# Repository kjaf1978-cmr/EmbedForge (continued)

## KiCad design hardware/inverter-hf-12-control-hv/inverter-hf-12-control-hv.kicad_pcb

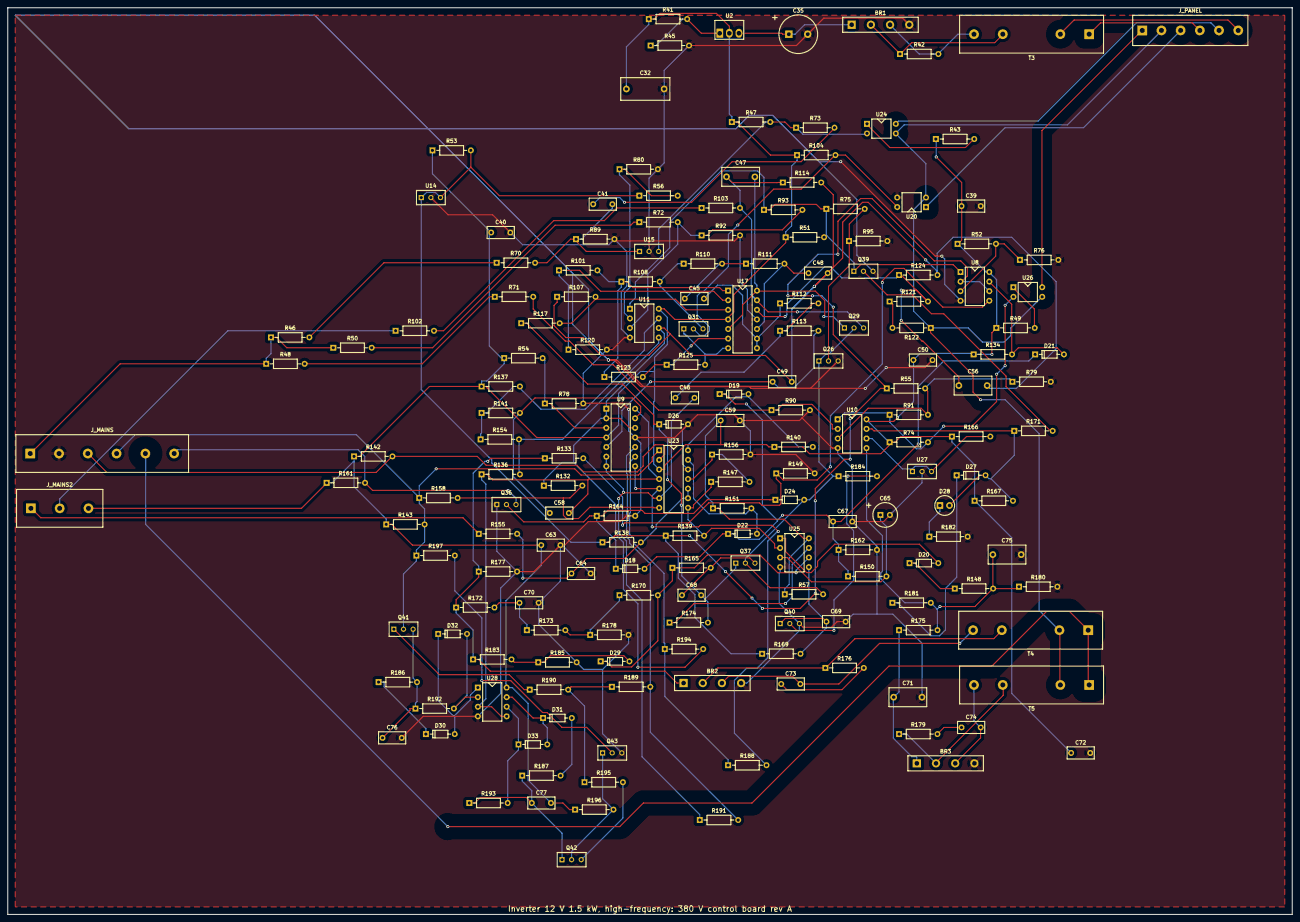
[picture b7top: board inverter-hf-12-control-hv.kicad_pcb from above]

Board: 2 copper layers, 340.0 x 240.0 mm, 181 parts (0 on the bottom side), 113 nets.

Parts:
BR1, BR2, BR3: DB107; Bridge_Inline_4
C32: 10u; C_Film_P10
C35: 47u; CP_Radial_D10
C39, C40, C41, C48, C50, C59, C63, C72, C73, C74: 100n; C_Disc_5.08
C45: 110n; C_Disc_5.08
C46: 270n; C_Disc_5.08
C47, C56, C71, C75: 2.2u; C_Film_P7.5
C49: 39n; C_Disc_5.08
C58: 3.3n; C_Disc_5.08
C64: 47p; C_Disc_5.08
C65: 22u; CP_Radial_D6.3
C67: 150p; C_Disc_5.08
C68: 220n; C_Disc_5.08
C69: 470n; C_Disc_5.08
C70, C76, C77: 1u; C_Disc_5.08
D18, D19, D20, D21, D22, D24, D27, D29, D30, D31, D32, D33: 1N4148; D_DO-35
D26: BZX55C3V3; D_DO-35
D28: red; LED_D5.0
J_MAINS: mains to the panel; TerminalBlock_1x6_P7.62
J_MAINS2: mains to the panel; TerminalBlock_1x3_P7.62
J_PANEL: to the panel; TerminalBlock_1x6
Q26, Q39, Q40, Q43: BC547B; TO-92_Wide
Q29, Q31, Q36, Q37, Q41, Q42: 2N7000; TO-92_Wide
R41: 240; R_Axial_0207
R42, R51, R54, R57, R76, R78, R80, R120, R123, R125, R136, R149, R155, R161, R171, R172, R181, R185, R196: 10k; R_Axial_0207
R43, R47, R137, R174, R177, R186, R187: 1k; R_Axial_0207
R45: 2.61k; R_Axial_0207
R46, R48, R50, R71, R72, R93: 750k; R_Axial_0207
R49, R142, R143, R148, R182: 4.7k; R_Axial_0207
R52: 42.2k; R_Axial_0207
R53, R74, R104, R132, R134, R140, R151, R166, R167: 2.2k; R_Axial_0207
R55: 17.4k; R_Axial_0207
R56: 1.54k; R_Axial_0207
R70: 732k; R_Axial_0207
R73: 33k; R_Axial_0207
R75, R95, R114, R124, R165, R197: 47k; R_Axial_0207
R79, R107, R162, R164, R169, R170, R184, R191, R194: 100k; R_Axial_0207
R89: 9.76k; R_Axial_0207
R90: 7.87k; R_Axial_0207
R91: 2M; R_Axial_0207
R92: 9.31k; R_Axial_0207
R101: 4.99k; R_Axial_0207
R102, R103, R121, R122: 2.2M; R_Axial_0207
R108, R176, R179: 220; R_Axial_0207
R110, R111, R112, R113: 22.1k; R_Axial_0207
R117, R188, R189: 200k; R_Axial_0207
R133: 54.9k; R_Axial_0207
R138: 90.9k; R_Axial_0207
R139: 86.6k; R_Axial_0207
R141: 13.3k; R_Axial_0207
R147: 7.5k; R_Axial_0207
R150: 220k; R_Axial_0207
R154: 38.3k; R_Axial_0207
R156: 6.19k; R_Axial_0207
R158, R192, R193: 1M; R_Axial_0207
R173: 57.6k; R_Axial_0207
R175: 68k; R_Axial_0207
R178: 25.5k; R_Axial_0207
R180: 11.3k; R_Axial_0207
R183: 47.5k; R_Axial_0207
R190, R195: 470; R_Axial_0207
T3: 6.2; Transformer_Wires_P7.62
T4, T5: 0.052; Transformer_Wires_P7.62
U2: LM317HV; TO-220_Vertical
U8, U10, U11: LM393; DIP-8
U9, U17: TL074; DIP-14
U14, U15: TL431B; TO-92_Wide
U20, U24, U26: PC817; DIP-4
U23: LM339; DIP-14
U25: LM358; DIP-8
U27: TL431; TO-92_Wide
U28: TL072; DIP-8

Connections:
ADJH: R41.2, R45.1, U2.1
BFL: Q39.2, R171.2
BHY: R132.2, R158.2, U23.7
BIB: Q43.2, R197.2
BOM: R48.2, R71.1
BOR: R55.2, R79.1, R91.2, U10.3
BOS: R71.2, R90.1, U10.2
BQEH: Q26.2, R75.2, R95.1
BSS: Q40.2, R184.2
BUV: R72.2, R92.1, R93.2, U11.3
EN: Q39.1, R51.2, R75.1, R93.1, U8.1, U11.1
ENL: J_PANEL.1, U26.4
ENN: D24.2, Q26.1, Q29.2, Q37.2, R57.2, R184.1
F1A: C45.1, R110.2, R111.1
F1B: C48.1, R111.2, U17.10
F1O: C45.2, R112.1, U17.8, U17.9
F2A: C46.1, R112.2, R113.1
F2B: C49.1, R113.2, U9.5
FBA: R43.2, U24.1
FBC: C41.1, R73.2
FBK: R47.2, R73.1, U15.3, U24.2
FBM: R46.2, R70.1
FBS: C41.2, R70.2, R89.1, U15.1
FEA: C68.1, Q37.3, R165.2
FLT: D27.2, D28.2, R167.2, R171.1, U10.7
GND: J_PANEL.2, R122.1, T4.2, T5.2, U20.2, U24.3, U26.3
H: R101.2, R108.1, R123.1, U17.1
HBUS: J_MAINS.1, R46.1, R48.1, R50.1
HN: R101.1, R120.1, U17.2
HP: R107.2, R117.2, U17.3
HVG: BR1.4, BR2.4, BR3.4, C32.2, C35.2, C39.2, C40.2, C50.2, C59.2, C63.2, C64.2, C65.2, C67.2, C69.2, C70.2, C71.2, C72.2, C75.2, C76.2, D26.2, J_MAINS.2, Q26.3, Q36.1, Q39.3, Q40.3, Q43.3, R45.2, R76.2, R78.2, R79.2, R80.2, R89.2, R90.2, R92.2, R95.2, R120.2, R149.2, R156.2, R162.2, R164.2, R177.2, R178.2, R180.2, R182.2, R185.2, U8.4, U9.11, U10.4, U11.4, U14.2, U15.2, U17.11, U20.3, U23.12, U25.4, U27.2, U28.4
INA: J_MAINS.3, R142.2, U23.2
INB: J_MAINS.4, Q41.2, R143.2, R158.1, R197.1, U23.1
INBN: Q42.2, Q43.1, R196.2
L: Q31.1, R125.2, U17.7
L50A: J_PANEL.3, U20.1
LA: J_PANEL.4, T3.1
LAT: D27.1, R181.1
LFA: D28.1, R182.1
LN: R123.2, R125.1, U17.6
NDA: R102.2, R103.1
NDC: C47.1, Q29.3, R103.2, R114.1, U17.13
NEA: D29.1, R165.1, R170.2, U25.6
NTI: C58.1, R141.2, U9.13
OCH: R139.2, R147.1, U23.8, U25.2
OCL: R147.2, R156.1, U23.11
OCN: D22.2, R151.2, U23.13
OCP: D19.2, R140.2, U23.14
OCS: C67.1, D18.2, D19.1, D21.1, D22.1, R150.1, R162.1
OLC: C65.1, R150.2, U25.3
OLO: D20.2, U25.1
OLS: D20.1, R148.1
OUTL: J_MAINS.5, T4.1, T5.1
OVA: R49.2, U26.1
OVC: D21.2, R134.2, U8.7
OVK: R74.2, R91.1, U10.1, U26.2
PDA: R121.1, R122.2
PDC: C56.1, R121.2, R124.1, U17.12
PKD: D30.2, D32.1, U28.1
PKN: D32.2, R192.2, U28.2
PKR: D30.1, R186.1
PKV: C76.1, Q41.3, R186.2, R192.1
PLA: D29.2, R183.2, R185.1
PST: R136.2, R154.2, U11.5
Q50H: Q31.2, R104.2, U20.4
REF: R188.2, U9.8, U23.5
SAO: BR2.2, R176.1, T4.3
SAP: BR3.2, R179.1, T5.3
SBO: BR2.3, C73.2, T4.4
SBP: BR3.3, C74.2, T5.4
SD: J_MAINS.6, Q36.3, R161.2
SEL: R189.1, R190.2, R195.1
SELP: Q41.1, R190.1
SELV: Q42.3, R195.2
SINE: C46.2, R191.1, U9.6, U9.7, U23.6
SNO: C73.1, R176.2
SNP: C74.1, R179.2
SO: R170.1, R173.2, R178.1
SP: C75.1, R148.2, R175.2, R180.1, R181.2, U10.5
SQ: Q31.3, R108.2, R110.1
SQT: R137.2, R141.1, R154.1, U11.7
SRC: J_MAINS2.1, R155.1
SRS: C64.1, R138.2, R155.2, U23.9, U23.10
STOP: D18.1, D24.1, Q36.2, R164.1
SUMN: R188.1, R194.1, U9.9
SUMP: R189.2, R191.2, U9.10
SWA: J_MAINS2.2, R102.1
TRI: C58.2, R136.1, U9.14, U23.4, U28.3, U28.5
ULS: R52.2, R76.1, U8.3
UVM: R50.2, R72.1
V15H: C32.1, C39.1, C40.1, C50.1, C59.1, C63.1, C72.1, C77.2, J_MAINS2.3, R41.1, R43.1, R47.1, R49.1, R51.1, R52.1, R53.1, R54.1, R57.1, R74.1, R104.1, R134.1, R137.1, R140.1, R142.1, R143.1, R151.1, R161.1, R166.1, R167.1, R196.1, U2.2, U8.8, U9.4, U10.8, U11.8, U17.4, U23.3, U25.8, U28.8
VA: C68.2, D26.1, Q37.1, R117.1, R174.2
VAO: R174.1, U25.7
VC: J_PANEL.5, U24.4
VLC: R133.2, R149.1, U8.5
VLD: D31.1, D33.2, U28.7
VLN: D33.1, R193.2, U28.6
VLOH: R56.2, R80.1, U11.2
VLR: D31.2, R187.2
VLV: C77.1, Q42.1, R187.1, R193.1
VME: C47.2, Q29.1, U17.5, U17.14
VMID: C48.2, C49.2, C56.2, R107.1, R114.2, R124.2, R132.1, R194.2, U9.1, U9.2, U9.12, U11.6
VMR: R54.2, R78.1, U9.3
VREF: R53.2, R55.1, R56.1, R138.1, R139.1, R169.1, U8.2, U8.6, U14.1, U14.3
VREF2: R166.2, U10.6, U27.1, U27.3
VRO: BR2.1, R133.1, R172.1, R177.1, R183.1
VSO: C70.1, R172.2, R173.1
VSP: BR3.1, C71.1, R175.1
VSS: C69.1, Q40.1, R169.2, U25.5
VXH: BR1.1, C35.1, U2.3
XA1: BR1.2, R42.1, T3.3
XA2: BR1.3, R42.2, T3.4
XB: J_PANEL.6, T3.2

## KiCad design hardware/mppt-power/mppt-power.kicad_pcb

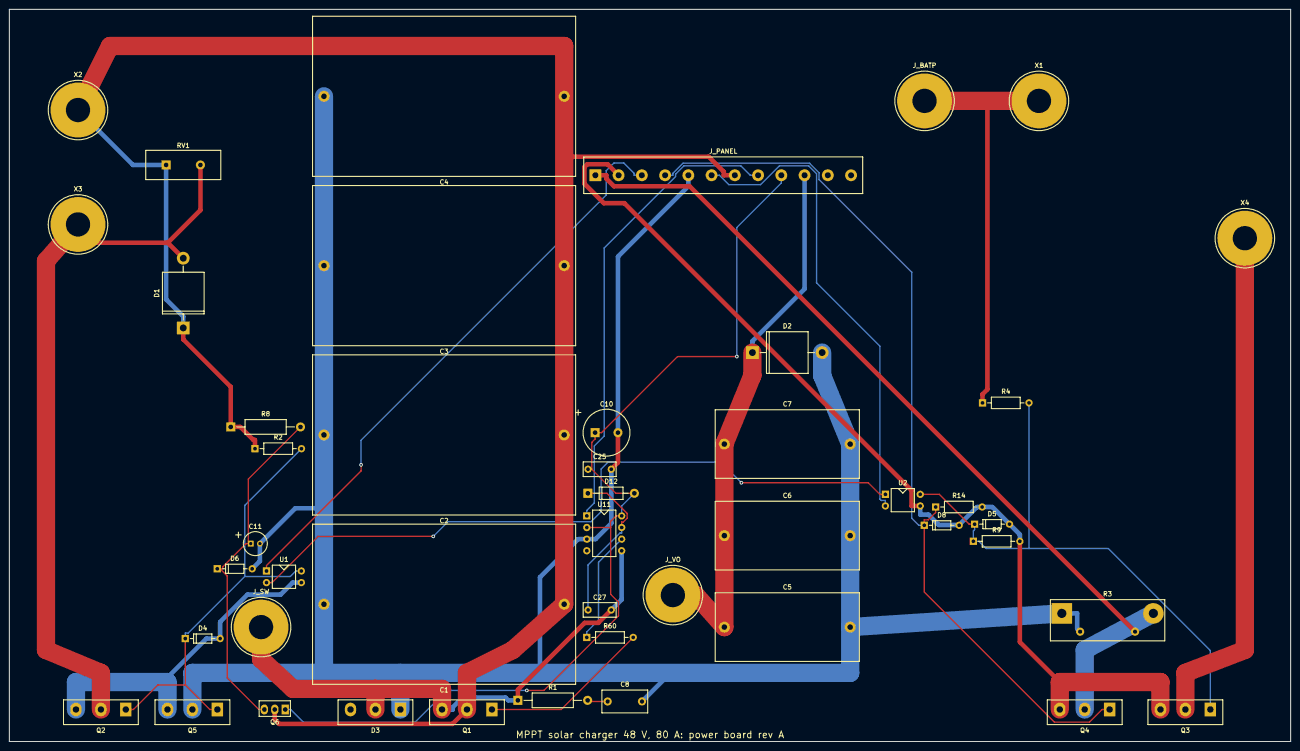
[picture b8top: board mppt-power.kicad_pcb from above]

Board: 2 copper layers, 280.0 x 160.0 mm, 46 parts (0 on the bottom side), 23 nets.

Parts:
C1, C2, C3, C4: 47u; C_Film_P52.5
C5, C6, C7: 47u; C_Film_P27.5
C8: 1n; C_Film_P7.5
C10: 100u; CP_Radial_D10
C11: 10u; CP_Radial_D5
C25, C27: 1u; C_Disc_5.08
D1: 5KP130CA; D_P600
D2: 5KP64A; D_P600
D3: STTH6003; TO-247_Vertical
D4, D5, D8: BZX55C12; D_DO-35
D6: BZX55C13; D_DO-35
D12: 1N4007; D_DO-41
J_BATP: BATP; Lug_M5
J_PANEL: to the panel; TerminalBlock_1x12
J_SW: SW; Lug_M5
J_VO: VO; Lug_M5
Q1, Q2, Q5: IRFP4668; TO-247_Vertical
Q3, Q4: IRFP4468; TO-247_Vertical
Q6: MJE340; TO-126_Vertical
R1: 220; R_Axial_0309
R2, R4: 470k; R_Axial_0207
R3: 1m; R_Shunt_4T
R8: 22k; R_Axial_0309
R9: 1M; R_Axial_0207
R14: 100k; R_Axial_0207
R60: 10; R_Axial_0207
RV1: 14D201K; MOV_Disc_14
U1, U2: PC817; DIP-4
U11: IR2184-type 600 V; DIP-8
X1: BAT+; Lug_M5
X2: PV+; Lug_M5
X3: PV-; Lug_M5
X4: BAT-; Lug_M5

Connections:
BATP: J_BATP.1, R4.1, X1.1
BF: J_PANEL.1, Q4.2, R3.2, R3.4
BN: D5.2, D8.2, J_PANEL.2, Q3.3, Q4.3, R9.2, R14.2, U2.3
BNB: Q3.2, X4.1
FLT2: J_PANEL.3, U1.1
G1: Q1.1, R60.2
GB: D8.1, J_PANEL.4, Q4.1, R14.1
GB2: D5.1, Q3.1, R4.2, R9.1, U2.4
GND: C1.2, C2.2, C3.2, C4.2, C5.2, C6.2, C7.2, C8.2, C10.2, C11.2, C25.2, D2.2, D3.1, D6.2, J_PANEL.5, Q5.2, R3.1, R3.3, U11.3
GPV: D4.1, Q2.1, Q5.1, R2.2, U1.4
HO: R60.1, U11.6
LFA2: U1.2, U2.1
LFB: J_PANEL.6, U2.2
PVN: D1.2, Q2.2, RV1.2, X3.1
PVP: C1.1, C2.1, C3.1, C4.1, D1.1, J_PANEL.7, Q1.2, Q6.2, R2.1, R8.1, RV1.1, X2.1
PWM: J_PANEL.8, U11.1
SNB: C8.1, R1.2
SPV: D4.2, Q2.3, Q5.3, U1.3
SW: C27.2, D3.2, J_SW.1, Q1.3, R1.1, U11.5
V12: C10.1, C25.1, D12.2, J_PANEL.9, Q6.1, U11.2, U11.8
VB: C27.1, D12.1, U11.7
VO: C5.1, C6.1, C7.1, D2.1, J_PANEL.10, J_VO.1
ZA: C11.1, D6.1, Q6.3, R8.2
